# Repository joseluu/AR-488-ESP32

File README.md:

# MCP-AR-488-ESP32

## Intro and goal

The idea is to have AI help me build electronics. AI needs eyes, the eyes are the oscilloscope which is used through an MCP interface.

The IEEE-488 controler is meant to expose an HTTP API which in turn is used by the MCP server.

## Build

GPIB/IEEE-488 interface board for the **Tektronix TDS784A** oscilloscope, based on an ESP32 (Heltec WiFi Kit 32) with GPIB bus transceivers. The board plugs directly onto the instrument's Centronics 24-pin GPIB connector.

This project is inspired by the [AR-488](https://github.com/Twilight-Logic/AR488) Arduino GPIB adapter, redesigned around the ESP32 for WiFi capability and higher throughput. There are ESP32 projects, such as: https://github.com/douardda/AR488-ESP32 I discovered them after having finished this one. Other projects are using the prologic serial protocol, their hardware most likely may be reflashed with the firmware here.

There are a few quirks, however the PCB works, requiring some modifications (soldering):
* to supply 3.3V instead of 5.0 V to the MCP chip (because I used a V1 ESP32 board and I thought I had V2)
* add the I2C pullups
* remove 3mm from the left side to fit directly behind the TDS784
If you consider making it check the photos in the docs subdirectory. The gerber files I have used are in AR488_ESP32/Elecrow_manufacturing_v1.1.zip

The ESP32 USB can power the whole board, if you use it this way, no need to populate the barrel jack connector and power supply conditioning part (it has not been tested)

See file [IMPROVEMENTS_V2.md](IMPROVEMENTS_V2.md) for further improvements (which I may never implement myself)

## Design workflow and caveats

The PCB has been designed using AI as well, where claude is driving circuit-synth which in turn generates the kicad schematic. Routing has been handled manually.

Circuit-synth required a modification to work under Windows and git-bash (see my circuit-synth repo). Another circuit-synth
anoyance is that circuit-synth used hierachical connectors on the same sheet, this was giving warnings in the kicad rules checker.

When refreshing the circuit with circuitsynth, it uses a set of new internal identifiers, so when updating the PCB from the electrical schematic (F8) you must check the option "Re-link footprint ... from reference designators"

See file [AI_Assisted_design_workflow.md](AI_Assisted_design_workflow.md)

## Electrical architecture and implementation

See file [Electrical_Architecture.md](Electrical_Architecture.md)

The ESP32 board used is the Heltec Wifi Kit 32 (version 1), the V2 has the same pinout and can be used directly, however the V3 has different I2C pins and most likely will require adjustments to schematic and firmware.

The exposed plated area around is meant for to solder a shield to limit radiated EMI in the lab. Not tested. Shielding completely will also shield the Wifi, so at this point this is a half baked idea.

## Firmware and Software

### Hardware test
In directory hardware_test, a test firmware is available, it sends a 1ms pulse to each of the GPIB connector pins.

### Firmware
The firmware for the ESP32 implements an HTTP API json style server made available on Wifi, not the usual serial protocol.

### Host software
In firmware/test the send_gpib.py allows to exercise many features and get back entire curve data, notably in .csv format, example commands:
```
# getting curve data
uv run --with websockets python firmware/test/send_gpib.py --waveform --points 5000 --out csv --name wave --source CH2 192.168.xx.yy
# getting a screen copy in .tif format
uv run --with websockets python firmware/test/send_gpib.py 192.168.11.175 --hardcopy
```
#### downloaded CSV scope curve example

#### Screen copy through GPIB and host software send_gpib.py

#### Actual screen for comparison

#### Host software help (-h)
```
send_gpib.py -h
usage: send_gpib.py [-h] [--addr ADDR] [--timeout TIMEOUT] [--binary] [--waveform] [--hardcopy]
                    [--hardcopy-format {TIFF,BMP,BMPCOLOR,PCX,PCXCOLOR,RLE}] [--hardcopy-layout {PORTRAIT,LANDSCAPE}]
                    [--hardcopy-palette {COLOR,MONOCHROME,INKSAVER,HARDCOPY}] [--points POINTS] [--start-index START_INDEX]
                    [--end-index END_INDEX] [--chunk-bytes CHUNK_BYTES] [--source SOURCE] [--width {1,2}] [--name NAME] [--out OUT]
                    host [command]

Send GPIB SCPI commands to a Tek scope via the AR-488-ESP32 gateway.

The ESP32 hosts a JSON-over-WebSocket bridge at ws://<host>/ws. This
script handles the protocol so an operator (or AI agent) can issue
SCPI commands and capture waveforms directly from the shell.

Invocation
----------
    send_gpib.py <ip> <scpi-command>           # auto: query if '?' else write
    send_gpib.py <ip> --binary "<scpi>"        # force binary response
    send_gpib.py <ip> --waveform [options]     # capture waveform(s)
    send_gpib.py <ip> --hardcopy [options]     # capture screen (TIFF default)
    send_gpib.py --help                         # full per-flag help

Output files
------------
Named  <ISO_8601>_<name>[_<chN>].<ext>  where:
  ISO_8601 = YYYY-MM-DDTHH-MM-SS taken at capture start (Windows-safe)
  name     = --name (default 'waveform')
  ext      = controlled by --out: 'csv', 'bin', or 'csv,bin'
  Default for --waveform is csv; other commands write nothing unless
  --out bin is given.

CSV layout
----------
    meta_key, meta_value, sample, raw_chN..., time_s, voltage_v_chN...
- Cols 1-2 hold scope state: date, hour, *IDN?, horizontal/trigger
  setup, then per-channel scale/offset/coupling/etc. Failed queries
  are silently dropped from this block.
- 'sample' is the 1-based scope record index.
- time_s/voltage_v_* are present only when WFMPRE? succeeds.

Windowed / large captures
-------------------------
TDS784A supports up to 500 000 points per record (option 1M). Use
--start-index/--end-index (1-based inclusive) to crop in the
instrument via DATA:START / DATA:STOP - only the requested range
crosses the GPIB bus. Windows larger than --chunk-bytes (default
32 KiB) are chunked transparently to fit the gateway's 64 KiB buffer.

Examples
--------
    send_gpib.py 192.168.1.42 "*IDN?"
    send_gpib.py 192.168.1.42 "CH2:SCALE 500E-3"             # 500 mV/div
    send_gpib.py 192.168.1.42 "HORIZONTAL:MAIN:SCALE?"

    # Default 5 K-pt capture from CH1 -> <stamp>_waveform.csv
    send_gpib.py 192.168.1.42 --waveform

    # Two channels, both CSV and per-channel .bin
    send_gpib.py 192.168.1.42 --waveform --source CH1,CH2 --out csv,bin

    # Full 500 K-pt record at 16-bit, custom name
    send_gpib.py 192.168.1.42 --waveform --points 500000 --width 2 --name run42

    # Sub-window 100k..105k from a 500 K record (5 K samples on the wire)
    send_gpib.py 192.168.1.42 --waveform --points 500000 \
                 --start-index 100000 --end-index 105000

    # Screen hardcopy as TIFF -> <stamp>_screen.tif
    send_gpib.py 192.168.1.42 --hardcopy

    # Hardcopy as BMP color, custom name
    send_gpib.py 192.168.1.42 --hardcopy --hardcopy-format BMPCOLOR --name run42

    # Different scope GPIB address
    send_gpib.py 192.168.1.42 --addr 5 "*IDN?"

positional arguments:
  host                  AR-488-ESP32 IP or hostname (shown on the OLED)
  command               SCPI command (omit when using --waveform)

options:
  -h, --help            show this help message and exit
  --addr ADDR           GPIB primary address (default 1)
  --timeout TIMEOUT     GPIB timeout in ms
  --binary              Force binary_query action (response returned as raw bytes)
  --waveform            Capture a waveform: configures DATA:* and runs CURVE? per channel
  --hardcopy            Capture the scope screen as an image (default TIFF). Saved to <stamp>_<name>.<ext>.
  --hardcopy-format {TIFF,BMP,BMPCOLOR,PCX,PCXCOLOR,RLE}
                        HARDCOPY:FORMAT value (default TIFF)
  --hardcopy-layout {PORTRAIT,LANDSCAPE}
                        HARDCOPY:LAYOUT value (default PORTRAIT)
  --hardcopy-palette {COLOR,MONOCHROME,INKSAVER,HARDCOPY}
                        HARDCOPY:PALETTE value (default COLOR)
  --points POINTS       Default end-index when --end-index is not given (default 5000). Set to the scope's full record length (up
                        to 500000) to grab everything.
  --start-index START_INDEX
                        First record sample to transfer, 1-based (default 1). Maps to DATA:START.
  --end-index END_INDEX
                        Last record sample to transfer, 1-based inclusive (default --points). Maps to DATA:STOP.
  --chunk-bytes CHUNK_BYTES
                        Max bytes per CURVE? response; larger windows are split into chunks transparently (default 32768; the
                        gateway caps at ~64KiB).
  --source SOURCE       Source channel(s), comma-separated (default CH1, e.g. CH1,CH2)
  --width {1,2}         Bytes per sample, 1 or 2 (default 1)
  --name NAME           Stem for output files (default 'waveform' for --waveform, 'screen' for --hardcopy, 'capture' otherwise)
  --out OUT             Output formats, comma-separated: csv, bin. Default for --waveform is 'csv'; for other commands no file is
                        written.
```

## License

MIT

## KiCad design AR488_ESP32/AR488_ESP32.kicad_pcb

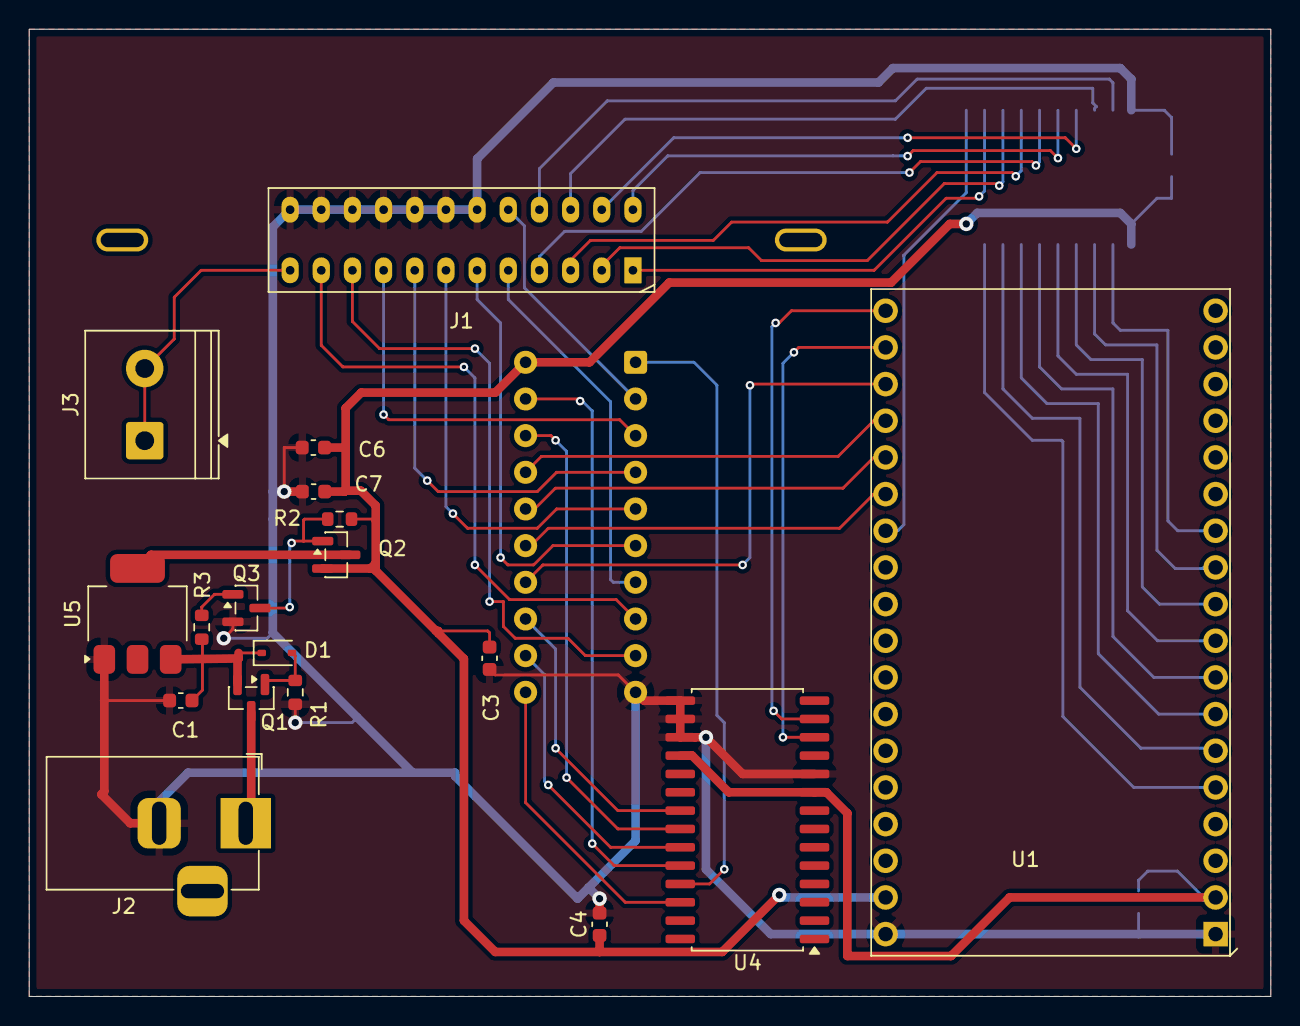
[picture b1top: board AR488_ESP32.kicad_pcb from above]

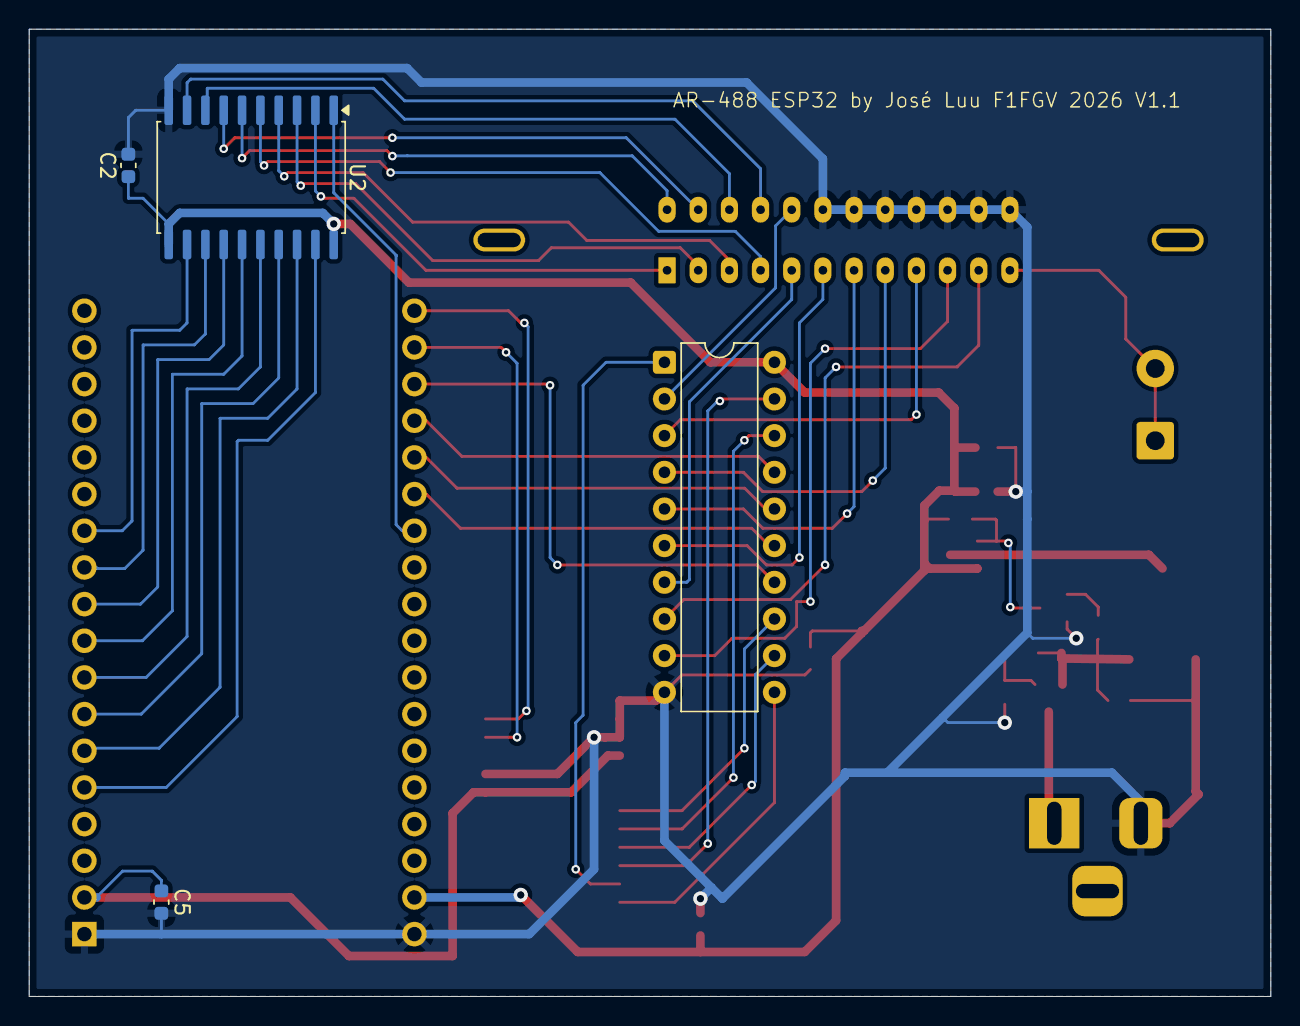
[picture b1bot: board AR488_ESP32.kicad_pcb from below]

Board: 2 copper layers, 86.0 x 67.0 mm, 22 parts (4 on the bottom side), 47 nets.

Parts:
C1: 10u; C_0603_1608Metric
C2, C3, C4, C5: 100n; C_0603_1608Metric
C6: 1u; C_0603_1608Metric
C7: 22u; C_0603_1608Metric
D1: MM3Z8V2; D_SOD-323
J1: GPIB_24; Centronics_24_GPIB_solder
J2: DC_7-12V; BarrelJack_Horizontal
J3: SHIELD; TerminalBlock_Phoenix_PT-1,5-2-5.0-H_1x02_P5.00mm_Horizontal
Q1, Q2: AO3401A; SOT-23
Q3: MMBT5551L; SOT-23
R1, R2: 100k; R_0603_1608Metric
R3: 10k; R_0603_1608Metric
U1: Heltec_WiFi_Kit_32_V2
U2: SN75160BDW; SOIC-20W_7.5x12.8mm_P1.27mm
U3: SN75161BN; DIP-20_W7.62mm
U4: MCP23017; SOIC-28W_7.5x17.9mm_P1.27mm
U5: AMS1117-5.0; SOT-223-3_TabPin2

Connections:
+3V3: C5.1, U1.3, U4.9 (VDD), U4.18 (~RESET)
+5V: C2.1, C3.1, C4.1, C6.1, C7.1, Q2.2 (S), R2.2, U1.4, U2.11 (~PE), U2.20 (VCC), U3.20 (VCC)
/ATN: U3.13 (ATN_T), U4.21 (GPA0)
/ATN_B: J1.11, U3.8 (ATN_B)
/DAV: U1.26, U3.15 (DAV_T)
/DAV_B: J1.6, U3.6 (DAV_B)
/DC: U3.11 (DC), U4.26 (GPA5)
/DIO1: U1.9, U2.19 (D1)
/DIO1_B: J1.1, U2.2 (B1)
/DIO2: U1.11, U2.18 (D2)
/DIO2_B: J1.2, U2.3 (B2)
/DIO3: U1.13, U2.17 (D3)
/DIO3_B: J1.3, U2.4 (B3)
/DIO4: U1.15, U2.16 (D4)
/DIO4_B: J1.4, U2.5 (B4)
/DIO5: U1.17, U2.15 (D5)
/DIO5_B: J1.13, U2.6 (B5)
/DIO6: U1.19, U2.14 (D6)
/DIO6_B: J1.14, U2.7 (B6)
/DIO7: U1.21, U2.13 (D7)
/DIO7_B: J1.15, U2.8 (B7)
/DIO8: U1.23, U2.12 (D8)
/DIO8_B: J1.16, U2.9 (B8)
/EOI: U1.32, U3.14 (EOI_T)
/EOI_B: J1.5, U3.7 (EOI_B)
/IFC: U3.18 (IFC_T), U4.22 (GPA1)
/IFC_B: J1.9, U3.3 (IFC_B)
/NDAC: U1.30, U3.17 (NDAC_T)
/NDAC_B: J1.8, U3.4 (NDAC_B)
/NRFD: U1.28, U3.16 (NRFD_T)
/NRFD_B: J1.7, U3.5 (NRFD_B)
/Q1_GATE: D1.2 (A), Q1.1 (G), R1.1
/Q2_GATE: Q2.1 (G), Q3.3 (C), R2.1
/Q3_BASE: Q3.1 (B), R3.2
/REN: U3.19 (REN_T), U4.24 (GPA3)
/REN_B: J1.17, U3.2 (REN_B)
/SCL: U1.34, U4.12 (SCK)
/SDA: U1.36, U4.13 (SDA)
/SHIELD: J1.12, J3.1, J3.2
/SRQ: U3.12 (SRQ_T), U4.23 (GPA2)
/SRQ_B: J1.10, U3.9 (SRQ_B)
/TE_CTRL: U3.1 (TE), U4.25 (GPA4)
/TE_DATA: U1.24, U2.1 (TE)
DC_7-12V: J2.1, Q1.3 (D)
GND: C1.2, C2.2, C3.2, C4.2, C5.2, C6.2, C7.2, J1.18, J1.19, J1.20, J1.21, J1.22, J1.23, J1.24, J2.2, Q3.2 (E), R1.2, U1.1, U1.2, U2.10 (GND), U3.10 (GND), U4.10 (VSS), U4.15 (A0), U4.16 (A1), U4.17 (A2), U5.1 (GND)
LDO_IN: C1.1, D1.1 (K), Q1.2 (S), R3.1, U5.3 (VI)
LDO_OUTPUT: Q2.3 (D), U5.2 (VO)

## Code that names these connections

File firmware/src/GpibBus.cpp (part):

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    13, 12, 14, 27, 26, 25, 33, 32
};

static constexpr uint8_t GPIO_DAV     = 5;
static constexpr uint8_t GPIO_NRFD    = 18;
static constexpr uint8_t GPIO_NDAC    = 23;
static constexpr uint8_t GPIO_EOI     = 19;
static constexpr uint8_t GPIO_TE_DATA = 17;

// --------------------------------------------------------------------------
// MCP23017 helpers.
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void GpibBus::setTalker() {
    if (talker_) return;

    // Drive handshake outputs to released BEFORE flipping TE_CTRL, so we
    // don't briefly assert DAV/EOI on the bus when SN75161B switches.
    digitalWrite(GPIO_DAV, HIGH);
    digitalWrite(GPIO_EOI, HIGH);
    pinMode(GPIO_DAV, OUTPUT);
    pinMode(GPIO_EOI, OUTPUT);
    pinMode(GPIO_NRFD, INPUT);
    pinMode(GPIO_NDAC, INPUT);

    digitalWrite(GPIO_TE_DATA, HIGH);           // SN75160B Talk (DIO out)
    setDataDir(true);

    mcpSetBitA(MCP_BIT_TE_CTRL, true);          // SN75161B handshake Talk
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    if (!talker_) return;

    // Pre-load the handshake outputs we'll be driving as listener.
    digitalWrite(GPIO_NRFD, LOW);               // not ready
    digitalWrite(GPIO_NDAC, LOW);               // not accepted
    pinMode(GPIO_NRFD, OUTPUT);
    pinMode(GPIO_NDAC, OUTPUT);
    pinMode(GPIO_DAV, INPUT);
    pinMode(GPIO_EOI, INPUT);

    digitalWrite(GPIO_TE_DATA, LOW);            // SN75160B Listen (DIO in)
    setDataDir(false);

    mcpSetBitA(MCP_BIT_TE_CTRL, false);         // SN75161B handshake Listen
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// Initialisation.

bool GpibBus::begin() {
    // Boot-strap safety: GPIO12 (DIO2) must be LOW. Done first so the
    // SN75160B can't back-drive it before we get TE_DATA defined.
    pinMode(12, OUTPUT);
    digitalWrite(12, LOW);

    pinMode(GPIO_TE_DATA, OUTPUT);
    digitalWrite(GPIO_TE_DATA, HIGH);           // SN75160B Talk

    // Default release state for the direct handshake outputs.
    pinMode(GPIO_DAV, OUTPUT);  digitalWrite(GPIO_DAV, HIGH);
    pinMode(GPIO_EOI, OUTPUT);  digitalWrite(GPIO_EOI, HIGH);
    pinMode(GPIO_NRFD, INPUT);
    pinMode(GPIO_NDAC, INPUT);
    setDataDir(true);                           // DIO outputs, released (HIGH)
    talker_ = true;

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bool GpibBus::writeByte(uint8_t b, bool eoi, uint32_t timeoutMs) {
    // wait NRFD released (HIGH = all listeners ready)
    uint32_t t0 = millis();
    while (digitalRead(GPIO_NRFD) == LOW) {
        if (millis() - t0 > timeoutMs) return false;
    }

    writeData(b);
    if (eoi) digitalWrite(GPIO_EOI, LOW);        // assert EOI
    delayMicroseconds(2);                        // T1 settle

    digitalWrite(GPIO_DAV, LOW);                 // assert DAV (data valid)

    // wait NDAC released (HIGH = all listeners accepted)
    t0 = millis();
    while (digitalRead(GPIO_NDAC) == LOW) {
        if (millis() - t0 > timeoutMs) {
            digitalWrite(GPIO_DAV, HIGH);
            if (eoi) digitalWrite(GPIO_EOI, HIGH);
            writeData(0xFF);                     // release DIO
            return false;
        }
    }

    digitalWrite(GPIO_DAV, HIGH);                // release DAV
    if (eoi) digitalWrite(GPIO_EOI, HIGH);
    writeData(0xFF);                             // release DIO between bytes
    return true;
}

bool GpibBus::readByte(uint8_t& b, bool& eoi, uint32_t timeoutMs) {
    // ready to receive
    digitalWrite(GPIO_NRFD, HIGH);

    // wait DAV asserted
    uint32_t t0 = millis();
    while (digitalRead(GPIO_DAV) == HIGH) {
        if (millis() - t0 > timeoutMs) {
            digitalWrite(GPIO_NRFD, LOW);
            return false;
        }
    }

    digitalWrite(GPIO_NRFD, LOW);                // not ready for next byte

    b = readData();
    eoi = (digitalRead(GPIO_EOI) == LOW);

    digitalWrite(GPIO_NDAC, HIGH);               // accepted

    // wait DAV released
    t0 = millis();
    while (digitalRead(GPIO_DAV) == LOW) {
        if (millis() - t0 > timeoutMs) {
            digitalWrite(GPIO_NDAC, LOW);
            return false;
        }
    }

    digitalWrite(GPIO_NDAC, LOW);                // back to not-accepted for next
    return true;
}

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        // Without a device on the bus, NDAC floats HIGH (bus pull-ups).
        uint32_t t0 = millis();
        while (millis() - t0 < timeoutMs) {
            if (digitalRead(GPIO_NDAC) == LOW) { present = true; break; }
            delay(1);
        }
        sendCommand(CMD_UNL);
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
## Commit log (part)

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2026-05-01 Version 1.1 working with firmware
2026-05-01 fix typo
2026-05-01 add details
2026-05-01 add more details
2026-05-01 add more files
2026-05-01 add reference
2026-05-02 reorder directories, improve firmware and host software, validate color screen copies
2026-05-02 final implementation plan for MCP server
2026-05-02 MCP server being tested
2026-05-02 Version 0.4, all MCP test passed
2026-05-02 fixed minor signal snapshot issue
2026-05-05 write a compatible tektool to extract firmware and tool to dump nvram
